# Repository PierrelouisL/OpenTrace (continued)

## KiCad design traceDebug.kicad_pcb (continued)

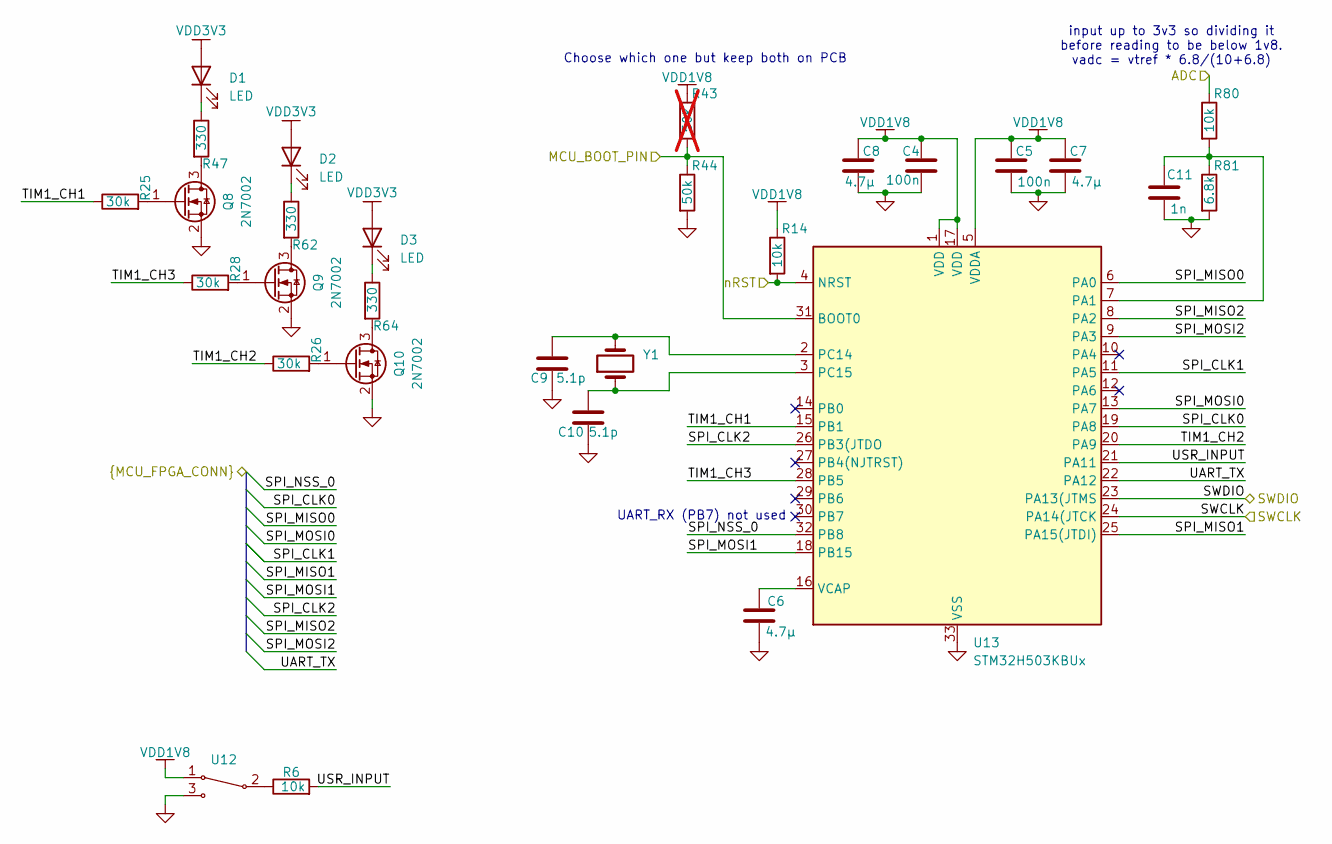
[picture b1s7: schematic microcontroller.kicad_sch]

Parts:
C4, C5: 100n; C_0402_1005Metric
C6, C7, C8: 4.7µ; C_0402_1005Metric
C9, C10: 5.1p; C_0402_1005Metric
C11: 1n; C_0402_1005Metric
D1, D2, D3: LED; D_0402_1005Metric
Q8, Q9, Q10: 2N7002; SOT-23
R6, R14, R80: 10k; R_0402_1005Metric
R25, R26, R28: 30k; R_0402_1005Metric
R43: 50k; R_0402_1005Metric; not fitted
R44: 50k; R_0402_1005Metric
R47, R62, R64: 330; R_0402_1005Metric
R81: 6.8k; R_0402_1005Metric
U12: C2906280
U13: STM32H503KBUx; QFN-32-1EP_5x5mm_P0.5mm_EP3.45x3.45mm
Y1: C19723454

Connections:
/DebugConnector/MCU_BOOT_PIN: R43.2, R44.1, U13.31 (BOOT0); also elsewhere on the board
/DebugConnector/SPI_CLK0: U13.19 (PA8); also elsewhere on the board
/DebugConnector/SPI_CLK1: U13.11 (PA5); also elsewhere on the board
/DebugConnector/SPI_CLK2: U13.26 (PB3(JTDO); also elsewhere on the board
/DebugConnector/SPI_MISO0: U13.6 (PA0); also elsewhere on the board
/DebugConnector/SPI_MISO1: U13.25 (PA15(JTDI)); also elsewhere on the board
/DebugConnector/SPI_MISO2: U13.8 (PA2); also elsewhere on the board
/DebugConnector/SPI_MOSI0: U13.13 (PA7); also elsewhere on the board
/DebugConnector/SPI_MOSI1: U13.18 (PB15); also elsewhere on the board
/DebugConnector/SPI_MOSI2: U13.9 (PA3); also elsewhere on the board
/DebugConnector/SPI_NSS_0: U13.32 (PB8); also elsewhere on the board
/DebugConnector/UART_TX: U13.22 (PA12); also elsewhere on the board
/DebugConnector/VTRef: R80.1; also elsewhere on the board
/DebugConnector/nRST: R14.2, U13.4 (NRST); also elsewhere on the board
/microcontroller/SWCLK: U13.24 (PA14(JTCK); also elsewhere on the board
/microcontroller/SWDIO: U13.23 (PA13(JTMS); also elsewhere on the board
/microcontroller/TIM1_CH1: R25.1, U13.15 (PB1)
/microcontroller/TIM1_CH2: R26.1, U13.20 (PA9)
/microcontroller/TIM1_CH3: R28.1, U13.28 (PB5)
/microcontroller/USR_INPUT: R6.2, U13.21 (PA11)
GND: C4.2, C5.2, C6.2, C7.2, C8.2, C9.1, C10.1, C11.2, Q8.2 (S), Q9.2 (S), Q10.2 (S), R44.2, R81.2, U12.3, U13.33 (VSS); also elsewhere on the board
unnamed: D1.1 (K), R47.1
unnamed: D2.1 (K), R62.1
unnamed: D3.1 (K), R64.1
unnamed: Q8.3 (D), R47.2
unnamed: Q8.1 (G), R25.2
unnamed: Q9.3 (D), R62.2
unnamed: Q9.1 (G), R28.2
unnamed: Q10.3 (D), R64.2
unnamed: Q10.1 (G), R26.2
unnamed: R6.1, U12.2
unnamed: C11.1, R80.2, R81.1, U13.7 (PA1)
unnamed: C9.2, U13.2 (PC14), Y1.2
unnamed: C10.2, U13.3 (PC15), Y1.1
unnamed: C6.1, U13.16 (VCAP)
VDD1V8: C4.1, C5.1, C7.1, C8.1, R14.1, R43.1, U12.1, U13.1 (VDD), U13.5 (VDDA), U13.17 (VDD); also elsewhere on the board
VDD3V3: D1.2 (A), D2.2 (A), D3.2 (A); also elsewhere on the board

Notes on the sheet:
Choose which one but keep both on PCB
UART_RX (PB7) not used
input up to 3v3 so dividing it before reading to be below 1v8. vadc = vtref * 6.8/(10+6.8)

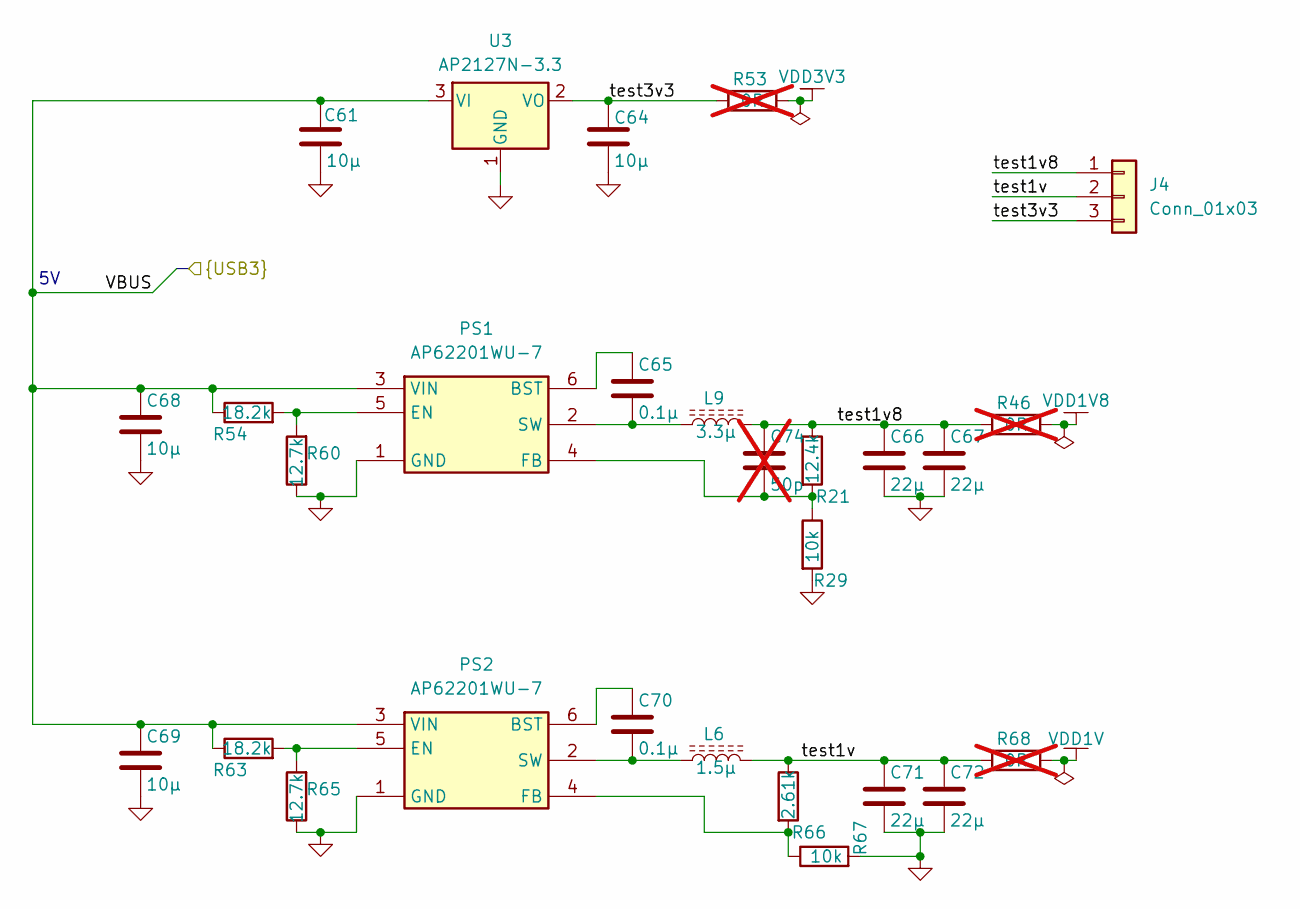
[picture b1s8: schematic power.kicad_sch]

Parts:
C61, C64, C68, C69: 10µ; C_0402_1005Metric
C65, C70: 0.1µ; C_0402_1005Metric
C66, C67, C71, C72: 22µ; C_0402_1005Metric
C74: 50p; C_0402_1005Metric; not fitted
J4: Conn_01x03; PinHeader_1x03_P2.54mm_Vertical
L6: 1.5µ; MTQH2016; LCSC C17701135
L9: 3.3µ; MTQH2016; LCSC C17701123
PS1, PS2: AP62201WU-7; SOT95P280X100-6N; Manufacturer_Part_Number AP62201WU-7; Mouser Part Number 621-AP62201WU-7
R21: 12.4k; R_0402_1005Metric
R29, R67: 10k; R_0402_1005Metric
R46, R68: 0R; R_0603_1608Metric; not fitted
R53: 0R; R_0402_1005Metric; not fitted
R54, R63: 18.2k; R_0402_1005Metric
R60, R65: 12.7k; R_0402_1005Metric
R66: 2.61k; R_0402_1005Metric
U3: AP2127N-3.3; SOT-23; LCSC C50314345

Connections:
/DebugConnector/VBUS: C61.1, C68.1, C69.1, PS1.3 (VIN), PS2.3 (VIN), R54.1, R63.1, U3.3 (VI); also elsewhere on the board
/Power/test1v: C71.1, C72.1, J4.2, L6.2, R66.1, R68.1
/Power/test1v8: C66.1, C67.1, C74.1, J4.1, L9.2, R21.1, R46.1
/Power/test3v3: C64.1, J4.3, R53.1, U3.2 (VO)
GND: C61.2, C64.2, C66.2, C67.2, C68.2, C69.2, C71.2, C72.2, PS1.1 (GND), PS2.1 (GND), R29.2, R60.1, R65.1, R67.2, U3.1 (GND); also elsewhere on the board
unnamed: C65.1, PS1.6 (BST)
unnamed: PS1.5 (EN), R54.2, R60.2
unnamed: C74.2, PS1.4 (FB), R21.2, R29.1
unnamed: C65.2, L9.1, PS1.2 (SW)
unnamed: C70.1, PS2.6 (BST)
unnamed: PS2.5 (EN), R63.2, R65.2
unnamed: PS2.4 (FB), R66.2, R67.1
unnamed: C70.2, L6.1, PS2.2 (SW)
VDD1V: R68.2; also elsewhere on the board
VDD1V8: R46.2; also elsewhere on the board
VDD3V3: R53.2; also elsewhere on the board

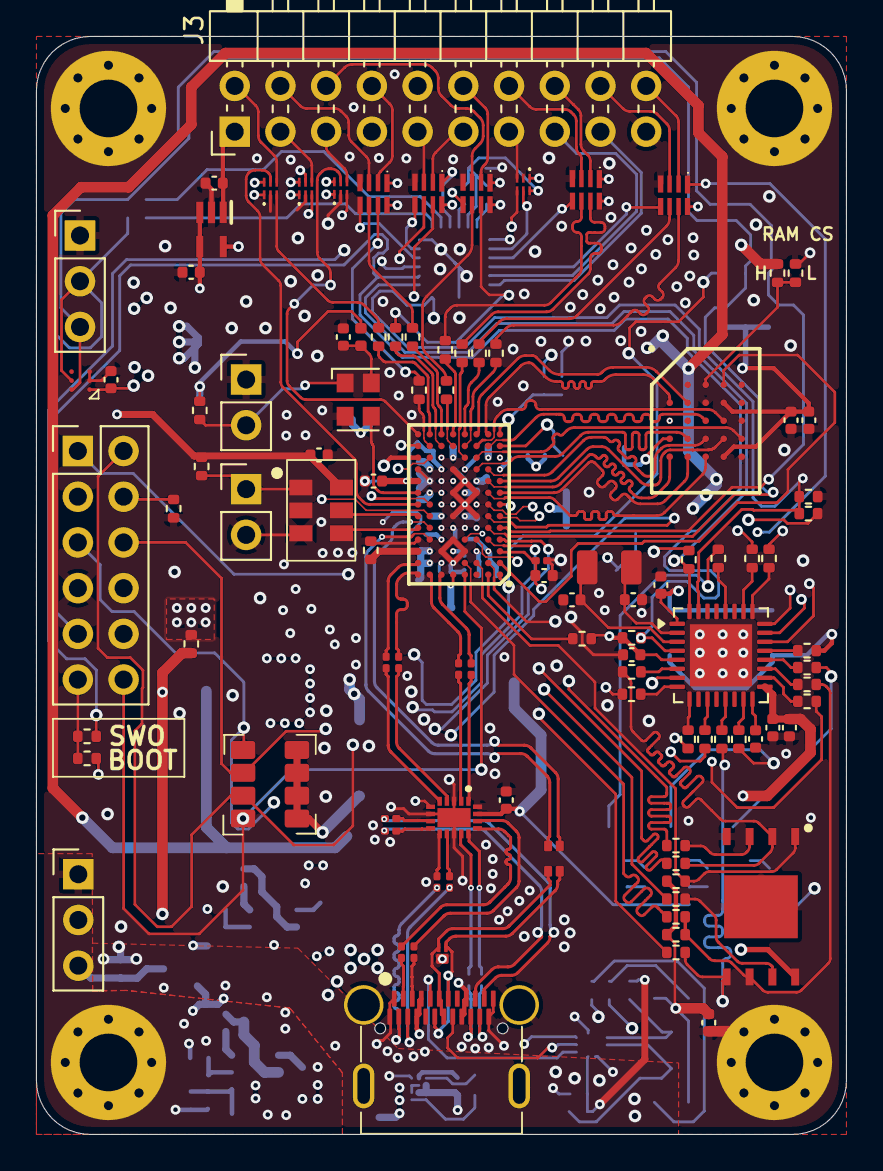
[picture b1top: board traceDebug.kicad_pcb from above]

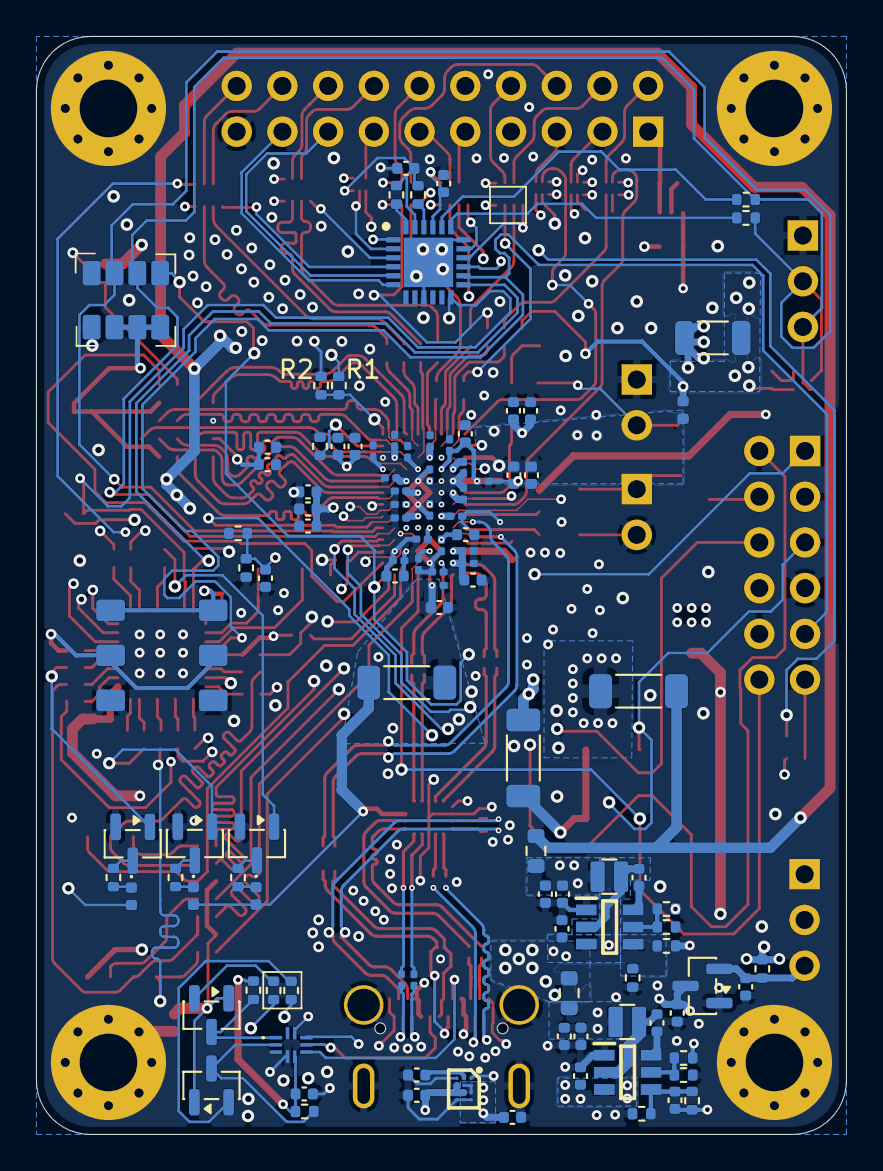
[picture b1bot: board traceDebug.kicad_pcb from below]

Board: 6 copper layers, 45.0 x 61.0 mm, 215 parts (109 on the bottom side), 196 nets.

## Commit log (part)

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2026-03-31 Pwr routing
